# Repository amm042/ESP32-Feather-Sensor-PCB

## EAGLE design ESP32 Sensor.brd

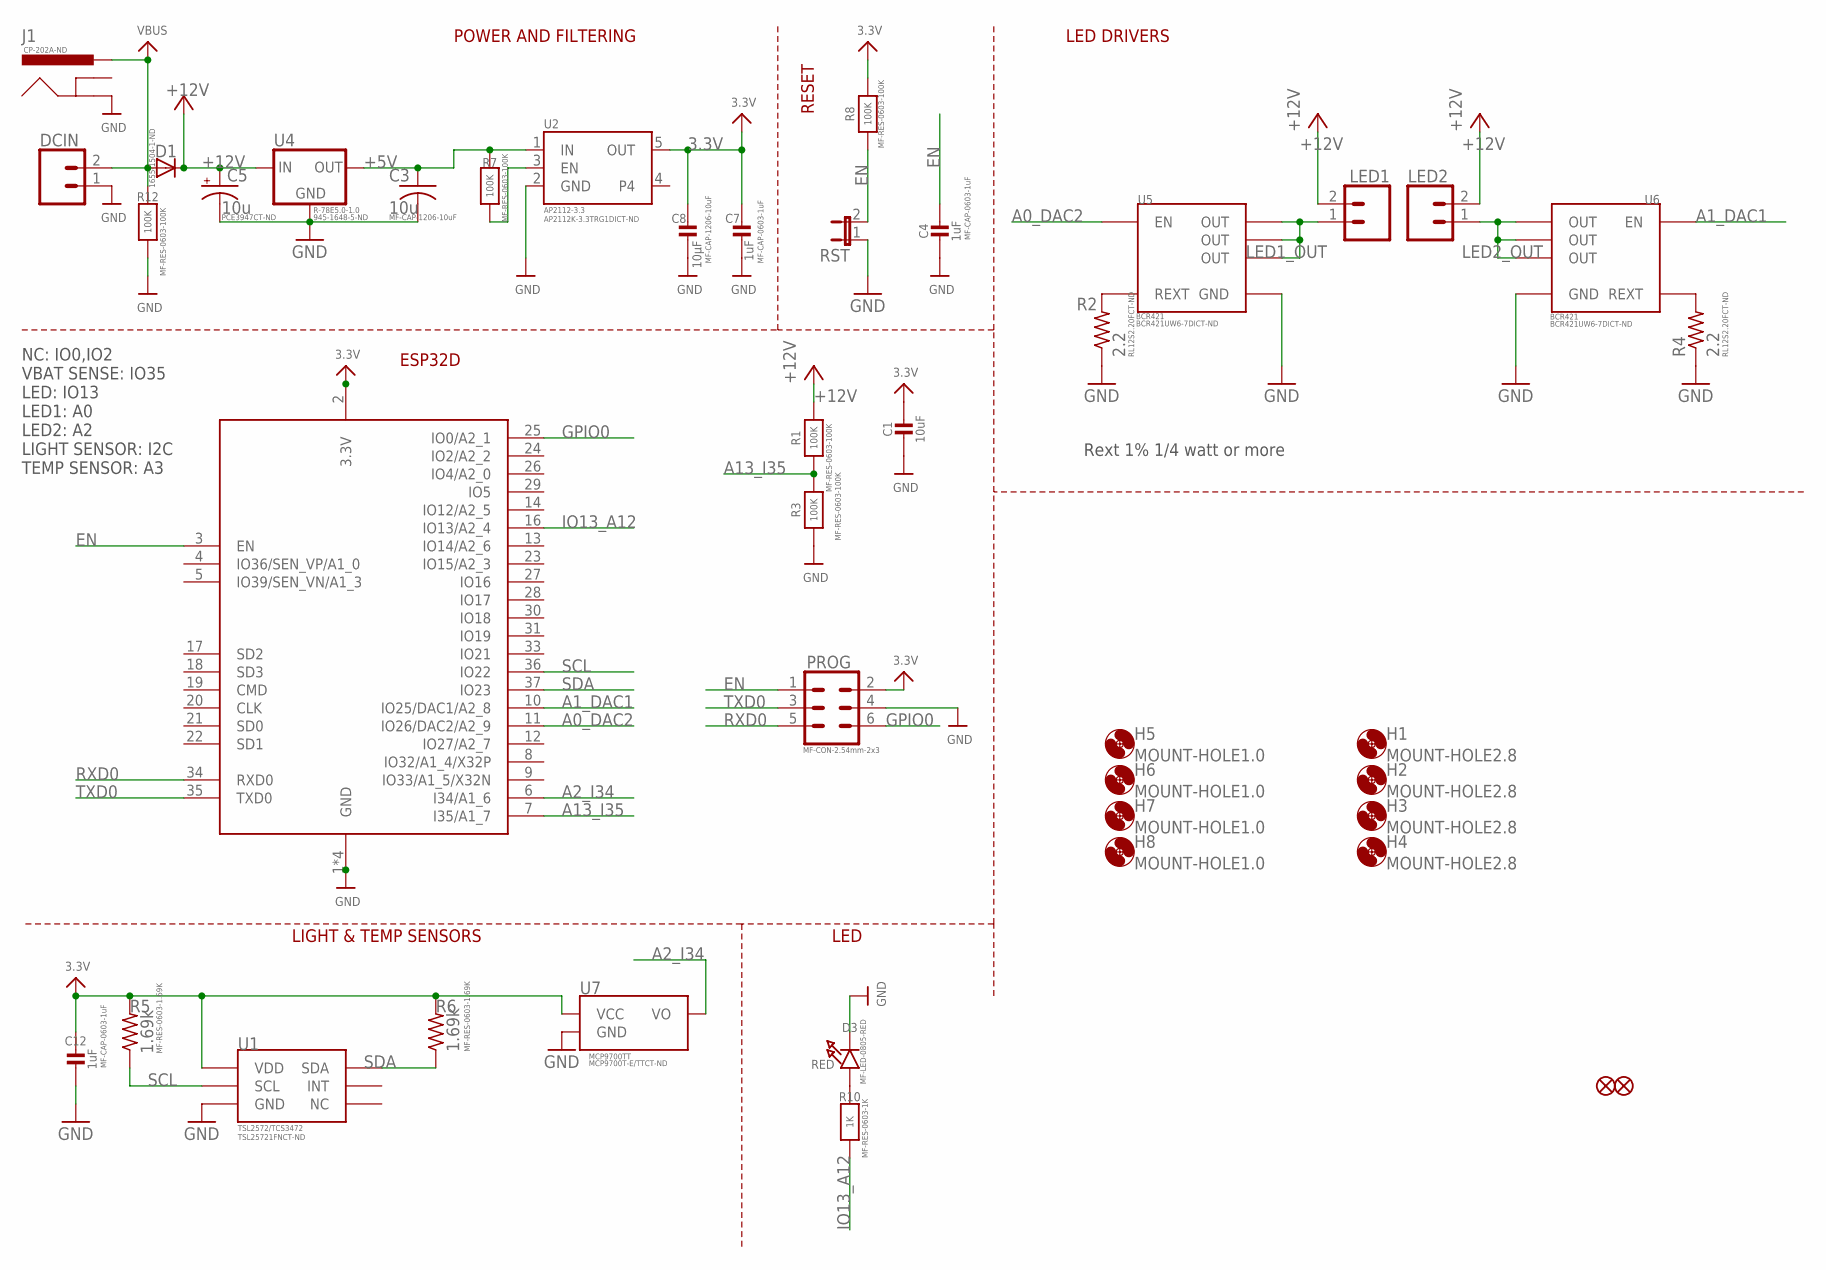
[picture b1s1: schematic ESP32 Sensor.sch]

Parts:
C1: 10uF; 0805-NO
C3: 10u; C1206
C4, C7, C12: 1uF; 0603-NO
C5: 10u; PANASONIC_C
C8: 10µF; _1206
D1: DIODE-DO214AC; DO214AC
D3: RED; CHIPLED_0805_NOOUTLINE
DCIN: CONN_023.5MM; SCREWTERMINAL-3.5MM-2
H1, H2, H3, H4: MOUNT-HOLE2.8; 2,8
H5, H6, H7, H8: MOUNT-HOLE1.0; 1,0
J1: POWER_JACKPTH_LOCK; POWER_JACK_PTH_LOCK
LED1, LED2: CONN_023.5MM; SCREWTERMINAL-3.5MM-2
PROG: CONN_03X2SHROUD; 2X3-SHROUDED
R1, R3, R7, R8, R12: 100K; 0603-NO
R2, R4: 2.2; R0603
R5, R6: 1.69k; R0603
R10: 1K; 0603-NO
RST: JP1E; JP1
U1: TSL2572/TCS3472; AMS_FN_6
U2: AP2112-3.3; SOT23-5
U3: ESP32_WROOM32_SKINNY; WROOM32_SKINNY
U4: R-78E5.0-1.0; DC-DC_CONVERTER_78XX
U5, U6: BCR421; SOT26
U7: MCP9700TT; SOT23-3
U$34, U$35: FIDUCIAL_1MM

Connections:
3.3V: C1.1, C7.1, C8.1, C12.1, PROG.2, R5.2, R6.2, R8.2, U1.P$1 (VDD), U2.5 (OUT), U3.2 (3.3V), U7.1 (VCC)
+5V: C3.1, R7.2, U2.1 (IN), U4.VOUT (OUT)
+12V: C5.+, D1.C, LED1.2, LED2.2, R1.2, U4.VIN (IN)
A0_DAC2: U3.11 (IO26/DAC2/A2_9), U5.1 (EN)
A1_DAC1: U3.10 (IO25/DAC1/A2_8), U6.1 (EN)
A2_I34: U3.6 (I34/A1_6), U7.2 (VO)
A13_I35: R1.1, R3.2, U3.7 (I35/A1_7)
EN: C4.1, PROG.1, R8.1, RST.2, U3.3 (EN)
GND: C1.2, C3.2, C4.2, C5.-, C7.2, C8.2, C12.2, D3.C, DCIN.1, J1.GND, PROG.4, R2.1, R3.1, R4.1, R12.1, RST.1, U1.P$3 (GND), U2.2 (GND), U3.1 (GND), U3.15 (GND), U3.38 (GND), U3.P$1 (GND), U4.GND, U5.4 (GND), U6.4 (GND), U7.3 (GND)
GPIO0: PROG.6, U3.25 (IO0/A2_1)
IO13_A12: R10.1, U3.16 (IO13/A2_4)
LED1_OUT: LED1.1, U5.2 (OUT), U5.3 (OUT), U5.5 (OUT)
LED2_OUT: LED2.1, U6.2 (OUT), U6.3 (OUT), U6.5 (OUT)
unnamed: R7.1, U2.3 (EN)
unnamed: R2.2, U5.6 (REXT)
unnamed: R4.2, U6.6 (REXT)
unnamed: D3.A, R10.2
RXD0: PROG.5, U3.34 (RXD0)
SCL: R5.1, U1.P$2 (SCL), U3.36 (IO22)
SDA: R6.1, U1.P$6 (SDA), U3.37 (IO23)
TXD0: PROG.3, U3.35 (TXD0)
VBUS: D1.A, DCIN.2, J1.PWR, R12.2

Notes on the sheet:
POWER AND FILTERING
RESET
LED DRIVERS
LIGHT & TEMP SENSORS
LED
ESP32D
NC: IO0,IO2 VBAT SENSE: IO35 LED: IO13 LED1: A0 LED2: A2 LIGHT SENSOR: I2C TEMP SENSOR: A3
Rext 1% 1/4 watt or more

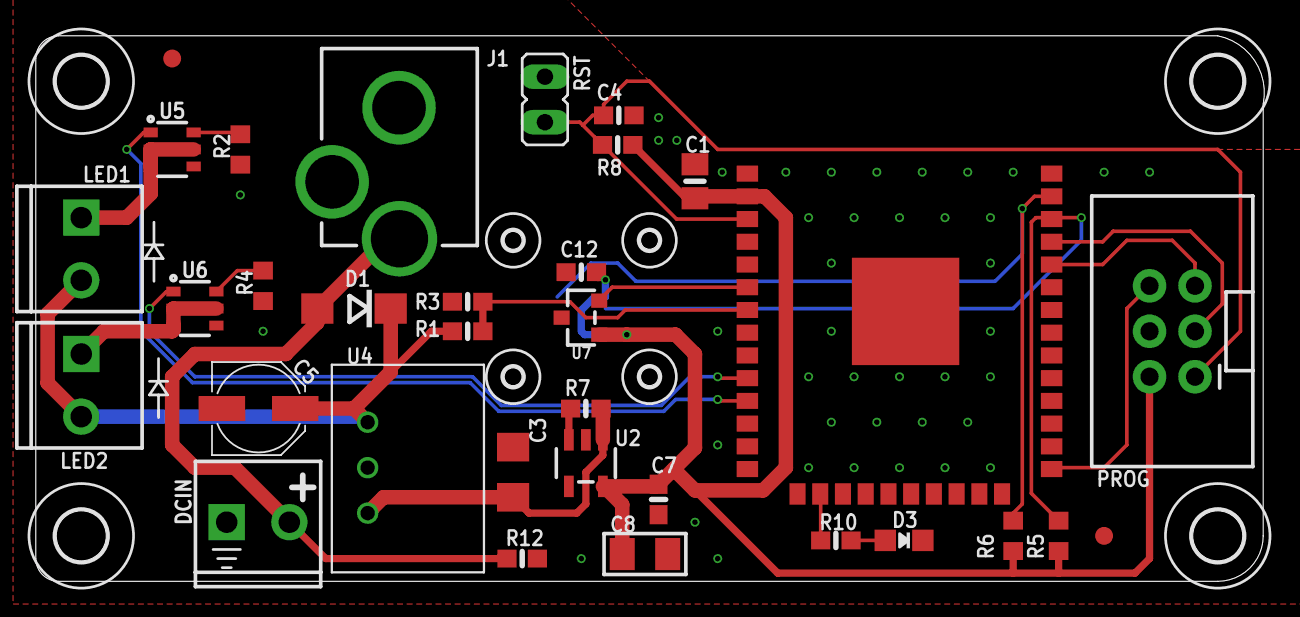
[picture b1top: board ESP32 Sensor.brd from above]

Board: 2 copper layers, 68.6 x 30.5 mm, 42 parts (1 on the bottom side), 22 nets.

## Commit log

2019-06-05 initial rev
2019-06-06 reva ordered
2019-06-28 checkin

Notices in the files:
parts and their libraries:
microbuilder: This work is placed in the public domain, and may be freely used for commercial and non-commercial work with the following conditions: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
SparkFun-IC-Power: Licensing: Creative Commons ShareAlike 4.0 International - https://creativecommons.org/licenses/by-sa/4.0
